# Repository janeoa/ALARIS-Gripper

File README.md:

# ALARIS Gripper project

* Mechanics
* Software
* PCBs

## GUI
The GUI is written in Go using Fyne. To run type `go run .` from `/GUI` directory

### binary
As every Go project can, you can build the project with `go build .`

### Dependancies
The `go.mod` file contains references for all used dependancies and you can download them with `go get .`

### Link to the Drive with the Model
There are two models presented: Solidworks and STL.
https://drive.google.com/file/d/1LMuIjnykMAK1zOiwv8W7WpgrKtq3R2hT/view?usp=sharing

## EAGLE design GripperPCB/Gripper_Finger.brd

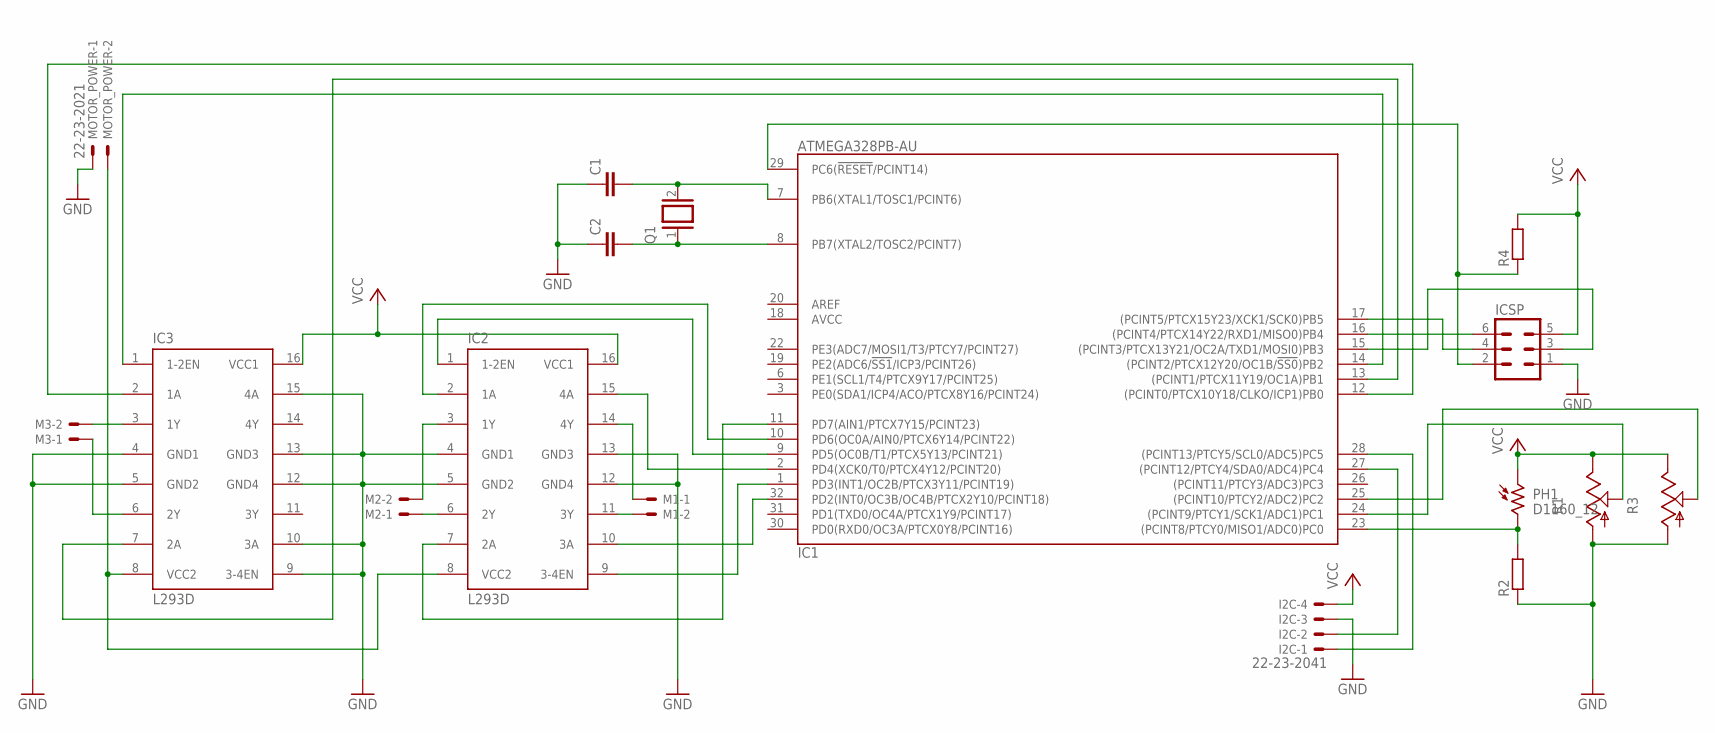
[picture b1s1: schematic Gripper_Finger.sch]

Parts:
C1, C2: C2.5/2; C2.5-2
I2C: 22-23-2041
IC1: ATMEGA328PB-AU; QFP32_7X7_0.80
IC2, IC3: L293D; DIL16
ICSP: MA03-2
M1, M2, M3: 22-23-2021
MOTOR_POWER: 22-23-2021
PH1: D1160_12; D11XX
Q1: XTAL/S; QS
R1, R3: TRIM_US-B64Y; B64Y
R2, R4: R-EU_0204/5; 0204/5

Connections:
AVCC: IC1.18 (AVCC)
CRYSTAL1: C2.2, IC1.8 (PB7(XTAL2/TOSC2/PCINT7)), Q1.1
CRYSTAL2: C1.2, IC1.7 (PB6(XTAL1/TOSC1/PCINT6)), Q1.2
GND: C1.1, C2.1, I2C.3, IC1.5 (GND), IC1.21 (GND), IC2.4 (GND1), IC2.5 (GND2), IC2.12 (GND4), IC2.13 (GND3), IC3.4 (GND1), IC3.5 (GND2), IC3.9 (3-4EN), IC3.10 (3A), IC3.12 (GND4), IC3.13 (GND3), IC3.15 (4A), ICSP.1, MOTOR_POWER.1, R1.A, R2.1, R3.A
LIGHT: IC1.23 ((PCINT8/PTCY0/MISO1/ADC0)PC0), PH1.2, R2.2
M1A: IC2.14 (4Y), M1.1
M1ASIG: IC1.2 (PD4(XCK0/T0/PTCX4Y12/PCINT20)), IC2.15 (4A)
M1B: IC2.11 (3Y), M1.2
M1BSIG: IC1.32 (PD2(INT0/OC3B/OC4B/PTCX2Y10/PCINT18)), IC2.10 (3A)
M1E: IC1.1 (PD3(INT1/OC2B/PTCX3Y11/PCINT19)), IC2.9 (3-4EN)
M2A: IC2.3 (1Y), M2.2
M2ASIG: IC1.10 (PD6(OC0A/AIN0/PTCX6Y14/PCINT22)), IC2.2 (1A)
M2B: IC2.6 (2Y), M2.1
M2BSIG: IC1.11 (PD7(AIN1/PTCX7Y15/PCINT23)), IC2.7 (2A)
M2E: IC1.9 (PD5(OC0B/T1/PTCX5Y13/PCINT21)), IC2.1 (1-2EN)
M3A: IC3.6 (2Y), M3.1
M3ASIG: IC1.13 ((PCINT1/PTCX11Y19/OC1A)PB1), IC3.7 (2A)
M3B: IC3.3 (1Y), M3.2
M3BSIG: IC1.12 ((PCINT0/PTCX10Y18/CLKO/ICP1)PB0), IC3.2 (1A)
M3E: IC1.14 ((PCINT2/PTCX12Y20/OC1B/!SS0!)PB2), IC3.1 (1-2EN)
MISO: IC1.16 ((PCINT4/PTCX14Y22/RXD1/MISO0)PB4), ICSP.6
MOSI: IC1.15 ((PCINT3/PTCX13Y21/OC2A/TXD1/MOSI0)PB3), ICSP.3
MOTOR_POWER: IC2.8 (VCC2), IC3.8 (VCC2), MOTOR_POWER.2
POT1: IC1.24 ((PCINT9/PTCY1/SCK1/ADC1)PC1), R1.S
POT2: IC1.25 ((PCINT10/PTCY2/ADC2)PC2), R3.S
RESET: IC1.29 (PC6(!RESET!/PCINT14)), ICSP.2, R4.1
SCK: IC1.17 ((PCINT5/PTCX15Y23/XCK1/SCK0)PB5), ICSP.4
SCL: I2C.1, IC1.28 ((PCINT13/PTCY5/SCL0/ADC5)PC5)
SDA: I2C.2, IC1.27 ((PCINT12/PTCY4/SDA0/ADC4)PC4)
VCC: I2C.4, IC1.4 (VCC), IC2.16 (VCC1), IC3.16 (VCC1), ICSP.5, PH1.1, R1.E, R3.E, R4.2

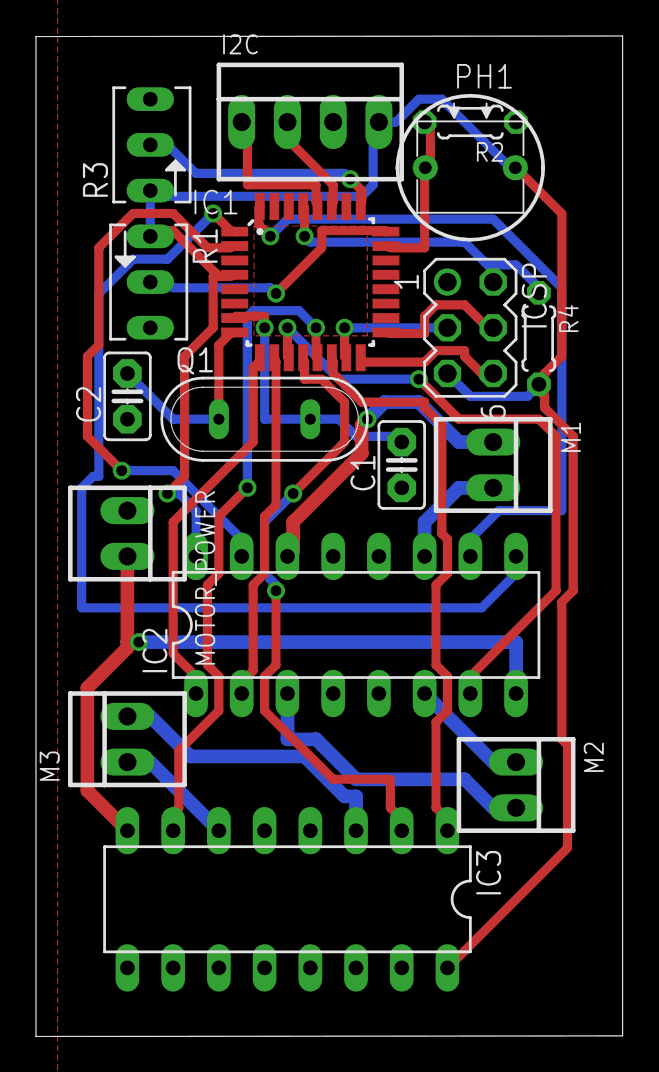
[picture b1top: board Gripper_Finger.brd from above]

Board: 2 copper layers, 32.6 x 55.6 mm, 17 parts (0 on the bottom side), 29 nets.

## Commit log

2021-05-24 init
2021-05-24 gitignore
2021-05-24 Eagle PCB init
2021-05-24 Arduino i2c init
2021-05-24 motor class
2021-05-24 board update with l293d
2021-05-24 formatting
2021-05-24 version 1.0.0 sent to engineering
2021-05-25 Update ledposition.ino
    Final Version
2021-05-26 Add files via upload
    Basic Functions seem to be ready
2021-05-26 added crystal
2021-05-26 layout with hole in rastnet under the uC
2021-05-27 Я создал отдельным проектам отдельные папки
2021-05-27 ignore CAMOUTPUTS
2021-05-27 tried I2C w/o crystal
2021-05-28 не помню :D
2021-05-28 comment
2021-06-03 direction of finger
2021-06-03 class lights with array
2021-06-03 dir func calc excel
2021-06-03 Slave roller motor class
2021-06-03 double digid buffer and refactored class
2021-06-04 restore
2021-06-04 +1 test condition for dir
2021-06-04 Presentable Stuff
    LEESSS GOOOOO
    we have main and slave
2021-06-08 pins
2021-06-09 fixed issue with single digid requests
2021-06-15 roller Class
2021-06-15 upds
2021-06-16 i2c sensor connection established. bug on Serial
2021-06-16 Serial bug fixed
2021-06-18 threshold to hard 400
    no calibration
2021-06-18 debug data via i2c
2021-06-18 finger 10 bit throttled data exchange
2021-06-21 Go fyne GUI init
2021-06-21 deleted depricated python code
2021-06-22 Simple layout of finger list
2021-06-23 finger pos + circle
2021-06-27 send/reset buttons on bottom
2021-06-27 Tappable bugged subcircle
2021-06-28 made two files and Gripper struct
2021-06-28 checking ports and reading
2021-06-28 auto reconnect device
2021-06-28 reconnect with status and simple send
2021-06-28 serial rate to 115200
2021-06-28 async read/write connected slaves
2021-06-28 send connected slaves
2021-06-28 cleanup the read/write
2021-06-30 refractor code into files
2021-06-30 removed tappable
2021-06-30 resizable layout for vmaxbox and circle
2021-06-30 logo
2021-06-30 fixed v2 compatability in container
2021-06-30 android first build
2021-06-30 more fluid layout
2021-06-30 exclude bluetooth audio
2021-07-01 callback to slave count
2021-07-02 set/reset active finger
2021-07-02 set newPos for sending
2021-07-07 newPos arrow indication
2021-07-07 entries change circle
2021-07-07 temporary no UART device list log
2021-07-07 new pos validation
2021-07-07 new pos auto routing started
2021-07-07 README Go update
2021-07-07 UPD-p: auto routing update
2021-07-07 BUGFIX: flickerring Connection status
2021-07-07 UPD: found slaves
2021-07-08 ADD: reset button func
2021-09-03 SAVE: before introdusing EasyTransfer
2021-09-03 SAVE
2021-09-07 EasyTransfer finger position
2021-09-07 deleted old build file
2021-09-07 ADD: redraw on fauld and redraw on refresh
2021-09-08 add new headphones to exception list
2021-09-08 FIN: pc to main ready
2021-09-08 FIN: EasyTransfer for finger
2021-09-13 FIN: sync work TODO: light sensor calib
2021-09-14 FIN: rott done. all work todo: fix stuck motors
2021-09-14 DEL: mac build
